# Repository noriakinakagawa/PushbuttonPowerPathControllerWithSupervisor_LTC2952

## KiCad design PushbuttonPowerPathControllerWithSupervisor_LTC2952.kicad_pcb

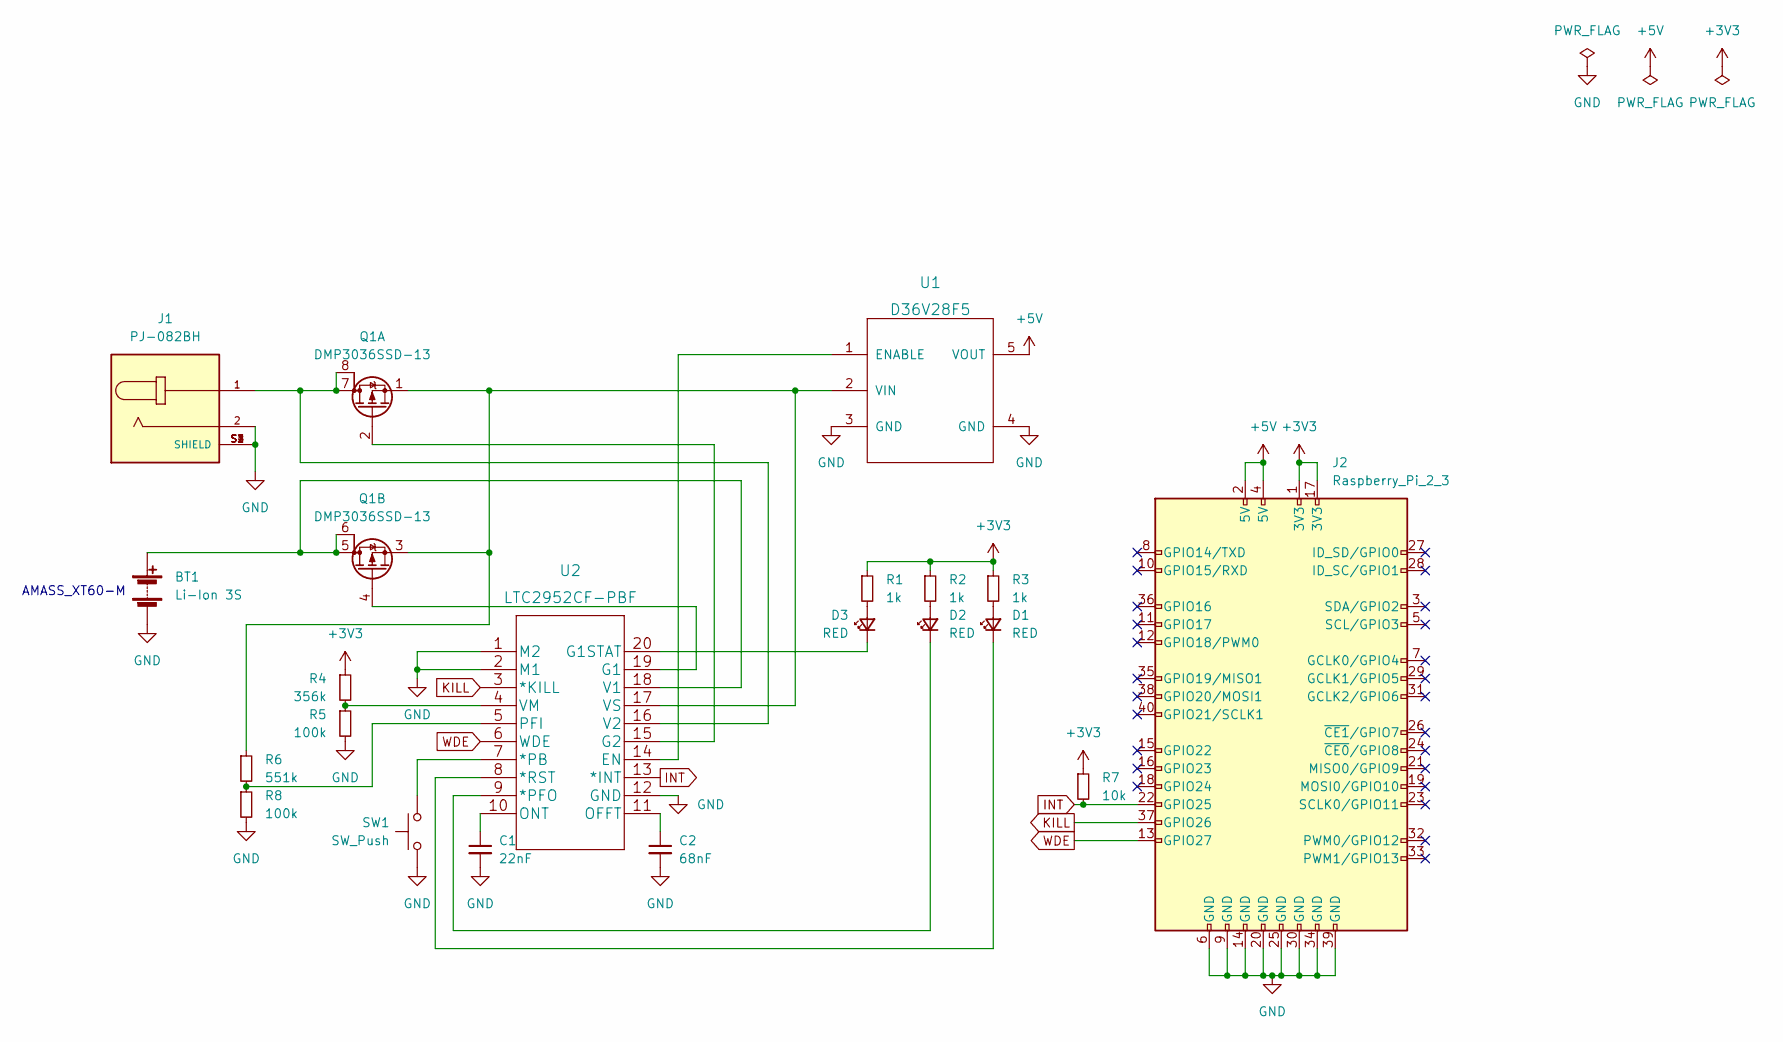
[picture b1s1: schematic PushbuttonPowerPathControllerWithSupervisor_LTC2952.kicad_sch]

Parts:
BT1: Li-Ion 3S; AMASS_XT60-M_1x02_P7.20mm_Vertical
C1: 22nF; C_0603_1608Metric
C2: 68nF; C_0603_1608Metric
D1, D2, D3: RED; LED_0603_1608Metric
J1: PJ-082BH; CUI_PJ-082BH
J2: Raspberry_Pi_2_3; PinSocket_2x20_P2.54mm_Vertical
Q1: DMP3036SSD-13; SOIC-8_3.9x4.9mm_P1.27mm
R1, R2, R3: 1k; R_0603_1608Metric
R4: 356k; R_0603_1608Metric
R5, R8: 100k; R_0603_1608Metric
R6: 551k; R_0603_1608Metric
R7: 10k; R_0603_1608Metric
SW1: SW_Push; SW_Tactile_SPST_Angled_PTS645Vx39-2LFS
U1: D36V28F5
U2: LTC2952CF-PBF

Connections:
+3V3: J2.1 (3V3), J2.17 (3V3), R1.1, R2.1, R3.1, R4.1, R7.1
+5V: J2.2 (5V), J2.4 (5V), U1.5 (VOUT)
GND: BT1.2 (-), C1.2, C2.2, J1.2, J1.S1 (SHIELD), J1.S2 (SHIELD), J1.S3 (SHIELD), J1.S4 (SHIELD), J2.6 (GND), J2.9 (GND), J2.14 (GND), J2.20 (GND), J2.25 (GND), J2.30 (GND), J2.34 (GND), J2.39 (GND), R5.2, R8.2, SW1.1, U1.3 (GND), U1.4 (GND), U2.1 (M2), U2.2 (M1), U2.12 (GND)
INT: J2.22 (GPIO25), R7.2, U2.13 (*INT)
KILL: J2.37 (GPIO26), U2.3 (*KILL)
unnamed: BT1.1 (+), Q1.5 (D), Q1.6 (G), U2.18 (V1)
unnamed: C1.1, U2.10 (ONT)
unnamed: C2.1, U2.11 (OFFT)
unnamed: D1.1 (K), U2.8 (*RST)
unnamed: D1.2 (A), R3.2
unnamed: D2.1 (K), U2.9 (*PFO)
unnamed: D2.2 (A), R2.2
unnamed: D3.1 (K), U2.20 (G1STAT)
unnamed: D3.2 (A), R1.2
unnamed: J1.1, Q1.7 (D), Q1.8 (G), U2.16 (V2)
unnamed: Q1.1 (S), Q1.3 (S), R6.1, U1.2 (VIN), U2.17 (VS)
unnamed: Q1.2 (G), U2.15 (G2)
unnamed: Q1.4 (G), U2.19 (G1)
unnamed: R4.2, R5.1, U2.4 (VM)
unnamed: R6.2, R8.1, U2.5 (PFI)
unnamed: SW1.2, U2.7 (*PB)
unnamed: U1.1 (ENABLE), U2.14 (EN)
WDE: J2.13 (GPIO27), U2.6 (WDE)

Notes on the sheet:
AMASS_XT60-M

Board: 2 copper layers, 20 parts (1 on the bottom side), 23 nets, no tracks yet.

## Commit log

2023-01-23 License
2023-01-24 BY-SA 4.0
2023-01-24 回路図コメント追記
